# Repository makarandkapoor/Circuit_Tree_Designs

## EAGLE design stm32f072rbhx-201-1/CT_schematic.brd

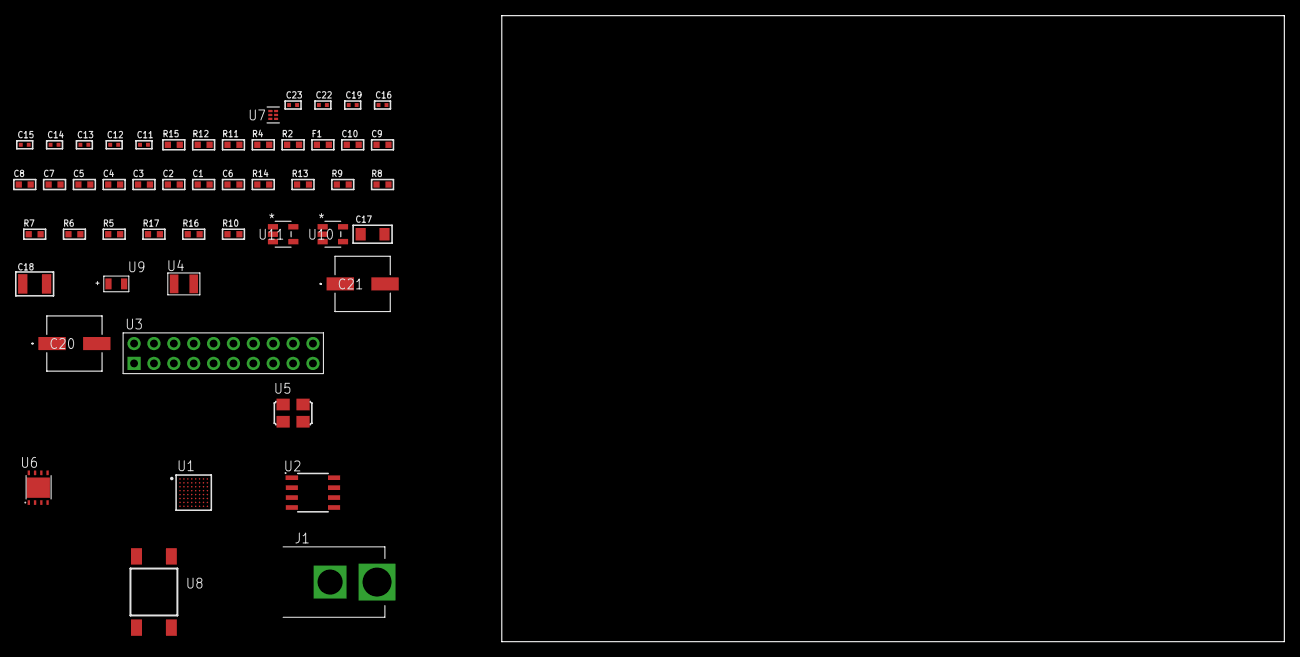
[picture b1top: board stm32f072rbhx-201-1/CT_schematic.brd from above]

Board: 2 copper layers, 100.0 x 80.0 mm, 51 parts (0 on the bottom side), 26 nets, no tracks yet.

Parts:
C1, C10: 1e-06; C0603
C2, C3, C4, C5, C7, C8: 1e-07; C0603
C6: 4.7e-06; C0603
C9: 1e-08; C0603
C11, C12: 1e-11; C0402
C13, C15, C16, C22, C23: 1e-08; C0402
C14, C19: 1e-07; C0402
C17: 1e-05; C1206
C18: 1e-05; C1210
C20, C21: 0.0001; EXV-9H
F1: 240.0; L0603
J1: PJ-037B; PJ-037B_PACKAGE
R2, R12: 1000.0; R0603
R4: 4700.0; R0603
R5, R6, R7, R8, R9, R13, R14: 10000.0; R0603
R10: 100000.0; R0603
R11: 2231.0; R0603
R15: 9100.0; R0603
R16: 680000.0; R0603
R17: 120000.0; R0603
U1: stm32f072rbh6; UFBGA64
U2: AT25020B-SSHL-T; SOIC-8
U3: TST-110-05-T-D-RA
U4: ABS07-32.768KHZ-7-T
U5: ASFL1-25MHZ-NCS; ASFL1
U6: LP3878SDX-ADJ/NOPB; WSON-8
U7: TPS3895ADRYR; SON-6
U8: 4-1437565-2; SW_4-1437565-2
U9: Q65110A2395; LGM67K-G1J2-24-Z
U10, U11: nc7sz125m5x; NC7SZ125M5X

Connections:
CLK_CRYSTAL_U1_A1: C11.1, U1.A1, U4.1
CLK_CRYSTAL_U1_B1: C12.1, U1.B1, U4.2
CLK_U1_C1: U1.C1, U5.3
GND: C1.2, C2.2, C3.2, C4.2, C5.2, C6.2, C7.2, C8.2, C9.2, C10.2, C11.2, C12.2, C13.2, C14.2, C15.2, C16.2, C17.2, C18.2, C19.2, C20.2, C21.2, C22.2, C23.2, J1.2, R2.2, R5.2, R12.2, R15.2, R17.2, U1.C2, U1.D4, U1.D5, U1.D6, U1.F1, U2.4, U3.4, U3.6, U3.8, U3.10, U3.12, U3.14, U3.16, U3.18, U3.20, U5.2, U6.3, U6.PAD, U7.2, U9.C, U10.2, U10.3, U11.1, U11.3
NET_U1_B4: R5.1, U1.B4
NET_U1_E1: R4.1, U1.E1, U11.4
NET_U1_H1: C9.1, C10.1, F1.1, U1.H1
NET_U1_H8: U8.3, U8.4
NET_U2_3: R6.1, U2.3
NET_U2_7: R8.1, U2.7
NET_U6_1: C16.1, U6.1
NET_U6_6: R11.2, R12.1, U6.6
NET_U6_8: R10.1, U6.8
NET_U7_1: R14.1, R15.1, U7.1
NET_U7_3: R16.2, R17.1, U7.3
NET_U7_4: R13.1, U7.4, U10.4, U11.2
NET_U8_1: R2.1, U8.1, U8.2
PROC_SPI1_MISO: U1.A4, U2.2
PROC_SPI1_MOSI: U1.C4, U2.5
PROC_SPI1_NSS: R7.1, U1.A6, U2.1
PROC_SPI1_SCK: U1.A5, U2.6
PROC_SYS_SWCLK: U1.A7, U3.9
PROC_SYS_SWDIO: U1.A8, U3.7
RST_OUT_U3_SRESET_B: R9.1, U3.15, U10.1
VCC_S1_10V3: C17.1, C20.1, C21.1, J1.1, R10.2, U6.4
VCC_TIER1_3V3: C1.1, C2.1, C3.1, C4.1, C5.1, C6.1, C7.1, C8.1, C13.1, C14.1, C15.1, C18.1, C19.1, C22.1, C23.1, F1.2, R4.2, R6.2, R7.2, R8.2, R9.2, R11.1, R13.2, R14.2, R16.1, U1.B2, U1.D2, U1.E4, U1.E5, U1.E6, U2.8, U3.1, U5.4, U6.5, U7.6, U10.5, U11.5

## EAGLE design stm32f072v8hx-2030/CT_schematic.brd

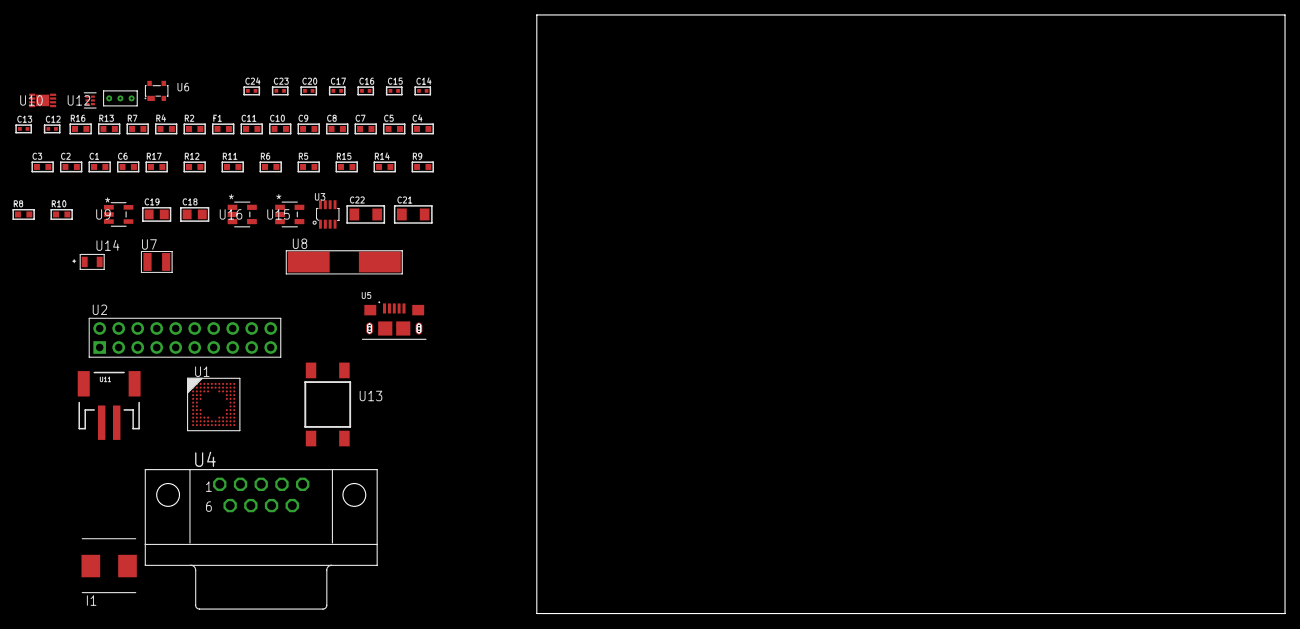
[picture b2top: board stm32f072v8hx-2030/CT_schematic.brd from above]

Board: 2 copper layers, 122.6 x 80.0 mm, 58 parts (0 on the bottom side), 34 nets, no tracks yet.

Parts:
C1, C11: 1e-06; C0603
C2, C3, C4, C5, C7, C8, C9: 1e-07; C0603
C6: 4.7e-06; C0603
C10: 1e-08; C0603
C12, C13, C14, C15: 1e-11; C0402
C16, C17, C20: 1e-07; C0402
C18, C19: 1e-05; C0805
C21, C22: 1e-05; C1206
C23, C24: 1e-08; C0402
F1: 240.0; L0603
I1: 2e-06; WE-HCI_7030/7040/7050
R2: 1000.0; R0603
R4: 4700.0; R0603
R5, R6, R11, R12, R17: 10000.0; R0603
R7: 120.0; R0603
R8: 100000.0; R0603
R9: 220000.0; R0603
R10: 1000000.0; R0603
R13: 9100.0; R0603
R14: 680000.0; R0603
R15: 120000.0; R0603
R16: 2000.0; R0603
U1: stm32f072v8h6; UFBGA100
U2: TST-110-05-T-D-RA
U3: MAX3051EKA+T; SOT-23-8
U4: 182-009-113R531; 182-009-MALE
U5: 10118193-0001LF; FCI_10118193-0001LF
U6: prtr5v0u2ax; SOT143B
U7: ABS07-32.768KHZ-7-T
U8: ABLS-25.000MHZ-B2F-T
U9: ltc3406es5; TSOT-23-5
U10: MCP73831T-2ACI/MC; DFN8_2X3MC
U11: S2B-PH-SM4-TB(LF)(SN); JST-2-SMD
U12: TPS3895ADRYR; SON-6
U13: 4-1437565-2; SW_4-1437565-2
U14: Q65110A2395; LGM67K-G1J2-24-Z
U15, U16: nc7sz125m5x; NC7SZ125M5X
U17: Dummy; DUMMY_PACKAGE_126

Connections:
CLK_CRYSTAL_U1_D1: C12.1, U1.D1, U7.1
CLK_CRYSTAL_U1_E1: C13.1, U1.E1, U7.2
CLK_CRYSTAL_U1_F1: C14.1, U1.F1, U8.1
CLK_CRYSTAL_U1_G1: C15.1, U1.G1, U8.2
GND: C1.2, C2.2, C3.2, C4.2, C5.2, C6.2, C7.2, C8.2, C9.2, C10.2, C11.2, C12.2, C13.2, C14.2, C15.2, C16.2, C17.2, C18.2, C19.1, C19.2, C20.2, C21.2, C22.2, C23.2, C24.2, R2.2, R5.2, R8.2, R9.2, R13.2, R15.2, R16.2, U1.D3, U1.F11, U1.F12, U1.K1, U2.4, U2.6, U2.8, U2.10, U2.12, U2.14, U2.16, U2.18, U2.20, U3.2, U4.5, U5.5, U5.6, U5.7, U5.8, U5.9, U6.1, U9.2, U10.6, U10.9, U11.2, U12.2, U14.C, U15.2, U15.3, U16.1, U16.3, U17.1
INPUT_USBPOWER_5V: C21.1, R17.2, U5.1, U6.4, U10.1, U10.2
NET_U1_A4: R5.1, U1.A4
NET_U1_H2: R4.1, U1.H2, U16.4
NET_U1_M1: C10.1, C11.1, F1.1, U1.M1
NET_U1_M12: U13.3, U13.4
NET_U3_6: R7.2, U3.6
NET_U3_8: R8.1, U3.8
NET_U4_2: R7.2, U3.6, U4.2
NET_U4_3: R7.1, U3.7, U4.3
NET_U9_3: I1.1, U9.3
NET_U9_5: R9.1, R10.1, U9.5
NET_U9_ATNET_3: I1.2, R10.2
NET_U10_5: R17.1, U10.5
NET_U10_8: R16.1, U10.8
NET_U12_1: R12.1, R13.1, U12.1
NET_U12_3: R14.2, R15.1, U12.3
NET_U12_4: R11.1, U12.4, U15.4, U16.2
NET_U13_1: R2.1, U13.1, U13.2
PROC_ADC_IN3: U1.L3, U17.3
PROC_ADC_IN13: U1.K2, U17.2
PROC_CAN_RX: U1.A3, U3.4
PROC_CAN_TX: U1.B3, U3.1
PROC_SYS_SWCLK: U1.A10, U2.9
PROC_SYS_SWDIO: U1.A11, U2.7
PROC_USB_DM: U1.B12, U5.2, U6.3
PROC_USB_DP: U1.A12, U5.3, U6.2
RST_OUT_U2_SRESET_B: R6.1, U2.15, U15.1
VCC_S1_3V7: C18.1, C22.1, U9.4, U10.3, U10.4, U11.1
VCC_TIER1_3V3: C1.1, C2.1, C3.1, C4.1, C5.1, C6.1, C7.1, C8.1, C9.1, C16.1, C17.1, C19.2, C20.1, C23.1, C24.1, F1.2, I1.2, R4.2, R6.2, R10.2, R11.2, R12.2, R14.1, U1.C4, U1.E2, U1.G11, U1.G12, U1.H3, U2.1, U3.3, U12.6, U15.5, U16.5

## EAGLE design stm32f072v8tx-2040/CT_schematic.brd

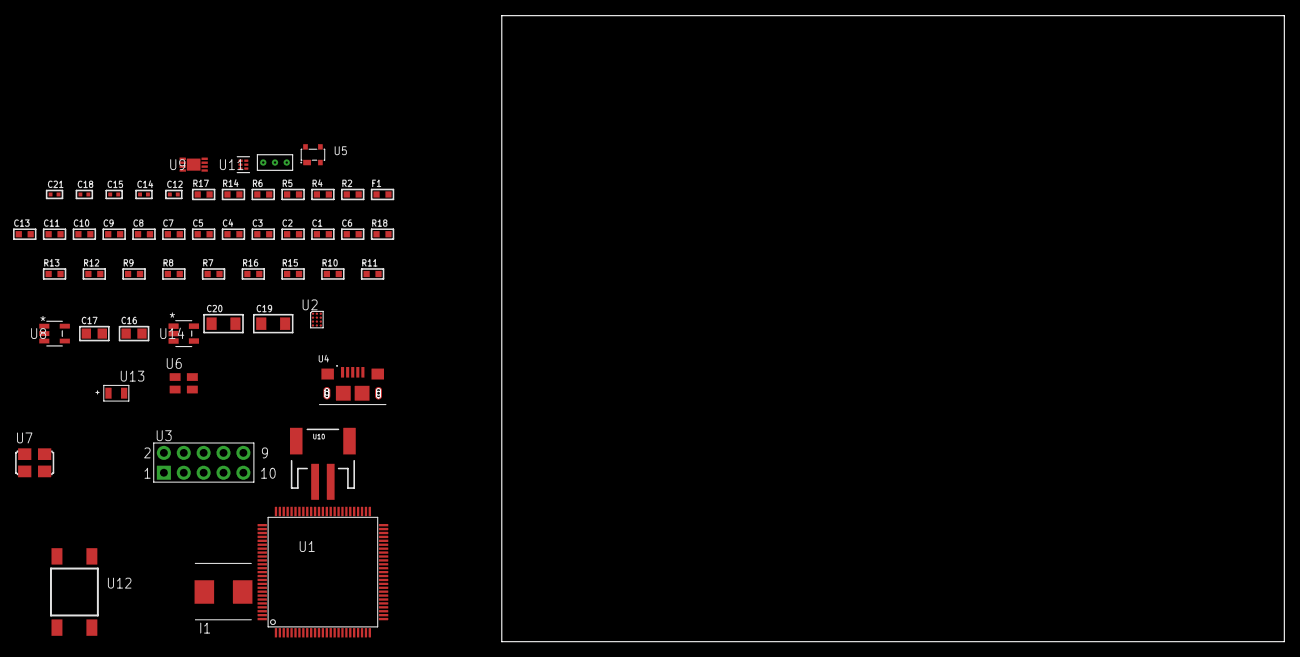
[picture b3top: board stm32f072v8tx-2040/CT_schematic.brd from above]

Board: 2 copper layers, 122.6 x 80.0 mm, 54 parts (0 on the bottom side), 31 nets, no tracks yet.

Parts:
C1, C11, C13: 1e-06; C0603
C2, C3, C4, C5, C7, C8, C9: 1e-07; C0603
C6: 4.7e-06; C0603
C10: 1e-08; C0603
C12, C18: 1e-07; C0402
C14, C15, C21: 1e-08; C0402
C16, C17: 1e-05; C0805
C19, C20: 1e-05; C1206
F1: 240.0; L0603
I1: 2e-06; WE-HCI_7030/7040/7050
R2: 1000.0; R0603
R4: 4700.0; R0603
R5, R6: 2200.0; R0603
R7, R8, R9, R12, R13, R18: 10000.0; R0603
R10: 220000.0; R0603
R11: 1000000.0; R0603
R14: 9100.0; R0603
R15: 680000.0; R0603
R16: 120000.0; R0603
R17: 2000.0; R0603
U1: stm32f072v8t6; LQFP100
U2: TSC2014IYZGT
U3: HTSS-105-01-G-D
U4: 10118193-0001LF; FCI_10118193-0001LF
U5: prtr5v0u2ax; SOT143B
U6: ASEK-32.768KHz-ECST; ASEK
U7: ASFL1-25MHZ-NCS; ASFL1
U8: ltc3406es5; TSOT-23-5
U9: MCP73831T-2ACI/MC; DFN8_2X3MC
U10: S2B-PH-SM4-TB(LF)(SN); JST-2-SMD
U11: TPS3895ADRYR; SON-6
U12: 4-1437565-2; SW_4-1437565-2
U13: Q65110A2395; LGM67K-G1J2-24-Z
U14: nc7sz125m5x; NC7SZ125M5X
U15: Dummy; DUMMY_PACKAGE_119

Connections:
CLK_U1_8: U1.8, U6.3
CLK_U1_12: U1.12, U7.3
GND: C1.2, C2.2, C3.2, C4.2, C5.2, C6.2, C7.2, C8.2, C9.2, C10.2, C11.2, C12.2, C13.2, C14.2, C15.2, C16.2, C17.1, C17.2, C18.2, C19.2, C20.2, C21.2, R2.2, R7.2, R10.2, R14.2, R16.2, R17.2, U1.20, U1.27, U1.49, U1.74, U1.99, U2.B2, U2.D2, U3.9, U4.5, U4.6, U4.7, U4.8, U4.9, U5.1, U6.2, U7.2, U8.2, U9.6, U9.9, U10.2, U11.2, U13.C, U14.1, U14.3, U15.1
INPUT_USBPOWER_5V: C19.1, R18.2, U4.1, U5.4, U9.1, U9.2
NET_U1_14: R4.1, U1.14, U14.4
NET_U1_21: C10.1, C11.1, F1.1, U1.21
NET_U1_92: R5.1, U1.92, U2.D1
NET_U1_93: R6.1, U1.93, U2.C1
NET_U1_94: R7.1, U1.94
NET_U1_98: U12.3, U12.4
NET_U2_B1: R9.1, U2.B1
NET_U2_C2: R8.1, U2.C2
NET_U3_3: U2.B3, U3.3
NET_U3_4: U2.D3, U3.4
NET_U3_5: U2.A3, U3.5
NET_U3_6: U2.C3, U3.6
NET_U8_3: I1.1, U8.3
NET_U8_5: R10.1, R11.1, U8.5
NET_U8_ATNET_3: I1.2, R11.2
NET_U9_5: R18.1, U9.5
NET_U9_8: R17.1, U9.8
NET_U11_1: R13.1, R14.1, U11.1
NET_U11_3: R15.2, R16.1, U11.3
NET_U11_4: R12.1, U11.4, U14.2
NET_U12_1: R2.1, U12.1, U12.2
PROC_TIM1_CH2: U1.42, U15.2
PROC_TIM1_CH4: U1.45, U15.3
PROC_USB_DM: U1.70, U4.2, U5.3
PROC_USB_DP: U1.71, U4.3, U5.2
VCC_S1_3V7: C16.1, C20.1, U8.4, U9.3, U9.4, U10.1
VCC_TIER1_3V3: C1.1, C2.1, C3.1, C4.1, C5.1, C6.1, C7.1, C8.1, C9.1, C12.1, C13.1, C14.1, C15.1, C17.2, C18.1, C21.1, F1.2, I1.2, R4.2, R5.2, R6.2, R8.2, R9.2, R11.2, R12.2, R13.2, R15.1, U1.6, U1.28, U1.50, U1.75, U1.100, U2.A2, U6.4, U7.4, U11.6, U14.5

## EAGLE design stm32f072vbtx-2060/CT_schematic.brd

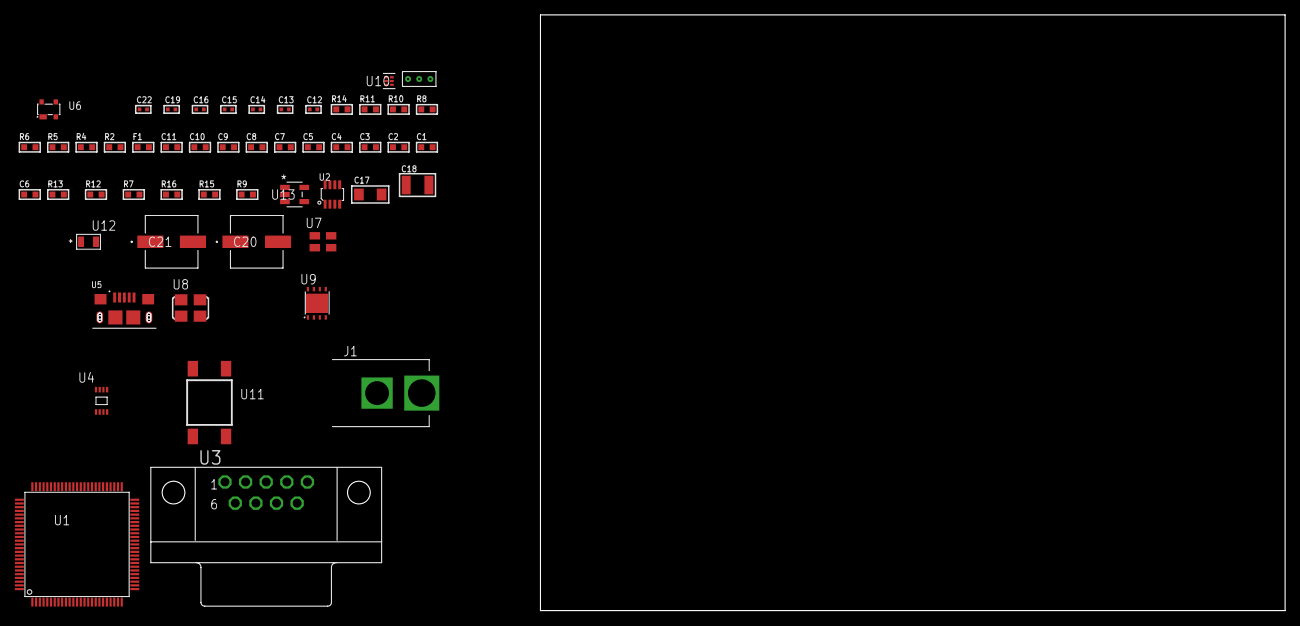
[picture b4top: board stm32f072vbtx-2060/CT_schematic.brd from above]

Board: 2 copper layers, 159.4 x 80.0 mm, 52 parts (0 on the bottom side), 29 nets, no tracks yet.

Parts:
C1, C11: 1e-06; C0603
C2, C3, C4, C5, C7, C8, C9: 1e-07; C0603
C6: 4.7e-06; C0603
C10: 1e-08; C0603
C12, C19: 1e-07; C0402
C13, C14, C15, C16, C22: 1e-08; C0402
C17: 1e-05; C1206
C18: 1e-05; C1210
C20, C21: 0.0001; EXV-9H
F1: 240.0; L0603
J1: PJ-037B; PJ-037B_PACKAGE
R2, R11: 1000.0; R0603
R4: 4700.0; R0603
R5, R6: 2200.0; R0603
R7, R12, R13: 10000.0; R0603
R8: 120.0; R0603
R9: 100000.0; R0603
R10: 2231.0; R0603
R14: 9100.0; R0603
R15: 680000.0; R0603
R16: 120000.0; R0603
U1: stm32f072vbt7; LQFP100
U2: MAX3051EKA+T; SOT-23-8
U3: 182-009-113R531; 182-009-MALE
U4: 24AA00T-I/MNY; TDFN-8/6MM
U5: 10118193-0001LF; FCI_10118193-0001LF
U6: prtr5v0u2ax; SOT143B
U7: ASEK-32.768KHz-ECST; ASEK
U8: ASFL1-25MHZ-NCS; ASFL1
U9: LP3878SDX-ADJ/NOPB; WSON-8
U10: TPS3895ADRYR; SON-6
U11: 4-1437565-2; SW_4-1437565-2
U12: Q65110A2395; LGM67K-G1J2-24-Z
U13: nc7sz125m5x; NC7SZ125M5X
U14: Dummy; DUMMY_PACKAGE_115

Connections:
CLK_U1_8: U1.8, U7.3
CLK_U1_12: U1.12, U8.3
GND: C1.2, C2.2, C3.2, C4.2, C5.2, C6.2, C7.2, C8.2, C9.2, C10.2, C11.2, C12.2, C13.2, C14.2, C15.2, C16.2, C17.2, C18.2, C19.2, C20.2, C21.2, C22.2, J1.2, R2.2, R7.2, R11.2, R14.2, R16.2, U1.20, U1.27, U1.49, U1.74, U1.99, U2.2, U2.8, U3.5, U4.4, U5.5, U5.6, U5.7, U5.8, U5.9, U6.1, U7.2, U8.2, U9.3, U9.PAD, U10.2, U12.C, U13.1, U13.3, U14.1
NET_U1_14: R4.1, U1.14, U13.4
NET_U1_21: C10.1, C11.1, F1.1, U1.21
NET_U1_75: C9.1, U1.75
NET_U1_92: R5.1, U1.92, U4.6
NET_U1_93: R6.1, U1.93, U4.5
NET_U1_94: R7.1, U1.94
NET_U1_98: U11.3, U11.4
NET_U2_6: R8.2, U2.6
NET_U3_2: R8.2, U2.6, U3.2
NET_U3_3: R8.1, U2.7, U3.3
NET_U6_4: U5.1, U6.4
NET_U9_1: C16.1, U9.1
NET_U9_6: R10.2, R11.1, U9.6
NET_U9_8: R9.1, U9.8
NET_U10_1: R13.1, R14.1, U10.1
NET_U10_3: R15.2, R16.1, U10.3
NET_U10_4: R12.1, U10.4, U13.2
NET_U11_1: R2.1, U11.1, U11.2
PROC_CAN_RX: U1.81, U2.4
PROC_CAN_TX: U1.82, U2.1
PROC_TIM1_CH2: U1.42, U14.2
PROC_TIM1_CH4: U1.45, U14.3
PROC_USB_DM: U1.70, U5.2, U6.3
PROC_USB_DP: U1.71, U5.3, U6.2
VCC_S1_7V6: C17.1, C20.1, C21.1, J1.1, R9.2, U9.4
VCC_TIER1_3V3: C1.1, C2.1, C3.1, C4.1, C5.1, C6.1, C7.1, C8.1, C12.1, C13.1, C14.1, C15.1, C18.1, C19.1, C22.1, F1.2, R4.2, R5.2, R6.2, R10.1, R12.2, R13.2, R15.1, U1.6, U1.28, U1.50, U1.100, U2.3, U4.8, U7.4, U8.4, U9.5, U10.6, U13.5

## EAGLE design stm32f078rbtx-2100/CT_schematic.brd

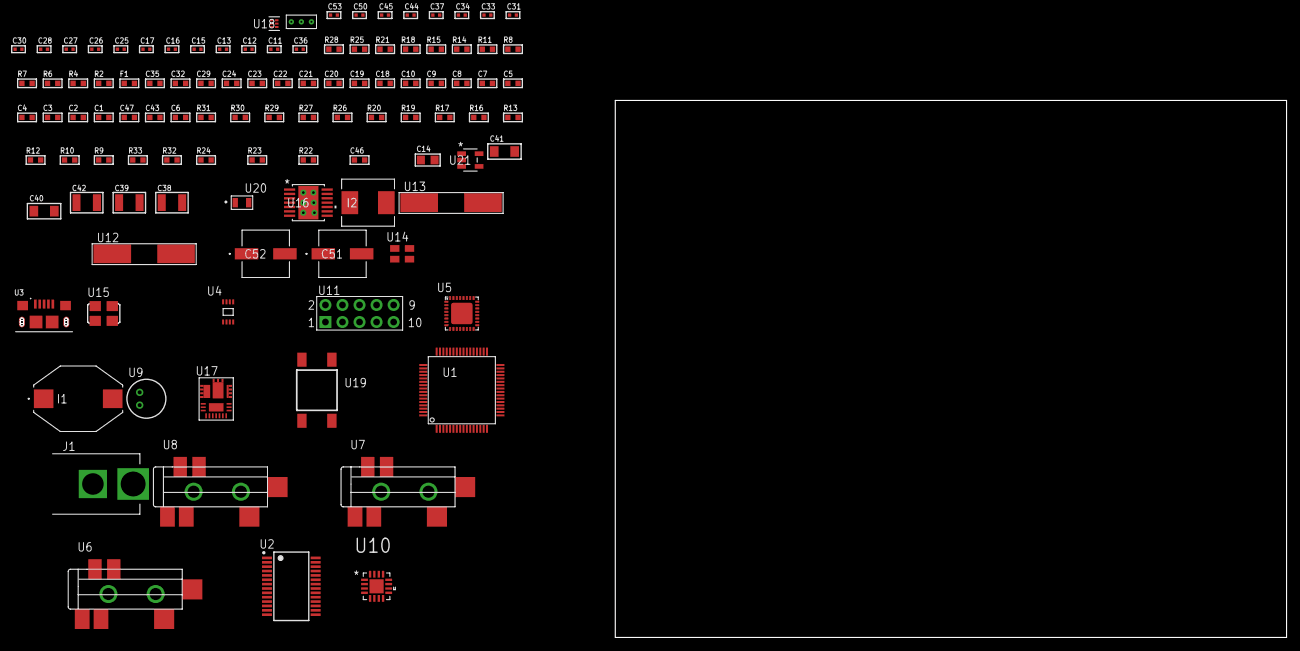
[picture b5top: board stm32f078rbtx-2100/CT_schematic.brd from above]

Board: 2 copper layers, 107 parts (0 on the bottom side), 73 nets, no tracks yet.

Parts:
C1, C10, C18, C19, C20, C21, C22, C23, C24, C29, C32, C35: 1e-06; C0603
C2, C3, C4, C5, C7, C8: 1e-07; C0603
C6: 4.7e-06; C0603
C9: 1e-08; C0603
C11, C12: 1e-11; C0402
C13, C15, C16, C25, C26, C27, C28, C30, C31, C37, C44, C45, C50: 1e-07; C0402
C14: 4.7e-06; C0805
C17, C33, C34, C53: 1e-08; C0402
C36: 3.3e-09; C0402
C38, C39: 2.2e-05; C1210
C40, C41: 1e-05; C1206
C42: 0.0001; C1210
C43: 2.2e-06; C0603
C46: 7.8444498006919e-09; R0603
C47: 2.7e-07; C0603
C51, C52: 0.0001; EXV-9H
F1: 240.0; L0603
I1: 1e-05; IND_PM3316
I2: 6.8e-07; IND25X25CZ
J1: PJ-037B; PJ-037B_PACKAGE
R2: 1000.0; R0603
R4, R11: 4700.0; R0603
R6, R7, R8: 2200.0; R0603
R9, R10, R12, R13, R16, R17, R29, R30: 10000.0; R0603
R14, R15: 1270.0; R0603
R18: 47.0; R0603
R19: 30000.0; R0603
R20: 22000.0; R0603
R21: 0.1; R0603
R22: 4030.2416170974; R0603
R23: 719.68600305311; R0603
R24: 64.984347826087; R0603
R25: 130.0; R0603
R26: 39000.0; R0603
R27: 49900.0; R0603
R28: 5600.0; R0603
R31: 82000.0; R0603
R32: 300000.0; R0603
R33: 120000.0; R0603
U1: stm32f078rbt7; LQFP64
U2: FT232RL-REEL; SSOP-28
U3: 10118193-0001LF; FCI_10118193-0001LF
U4: 24AA08T-I/MNY; TDFN-8/6MM
U5: SGTL5000XNAA3; QFN-32
U6, U7, U8: SJ-43515TS-SMT-TR
U9: WM-64PCT; WM-64PC
U10: TSC2013QRSARQ1; QFN65P400X400X100-17N
U11: HTSS-105-01-G-D
U12: ABLS-25.000MHZ-B2F-T
U13: ABLS-12.000MHZ-B4-T
U14: ASEK-2-32.768KHz-ECST; ASEK
U15: ASFL-24.57MHZ-NCS; ASFL1
U16: tps54225PWP; HTSSOP14
U17: IR3899MTR1PBF
U18: TPS3895ADRYR; SON-6
U19: 4-1437565-2; SW_4-1437565-2
U20: Q65110A2395; LGM67K-G1J2-24-Z
U21: nc7sz125m5x; NC7SZ125M5X
U22: Dummy; DUMMY_PACKAGE_213

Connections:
CLK_CRYSTAL_U1_5: C11.1, U1.5, U12.1
CLK_CRYSTAL_U1_6: C12.1, U1.6, U12.2
CLK_CRYSTAL_U2_27: U2.27, U13.1
CLK_CRYSTAL_U2_28: U2.28, U13.2
CLK_U1_3: U1.3, U14.3
CLK_U5_21: U5.21, U15.3
GND: C1.2, C2.2, C3.2, C4.2, C5.2, C6.2, C7.2, C8.2, C9.2, C10.2, C11.2, C12.2, C13.2, C14.2, C15.2, C16.2, C17.2, C25.2, C26.2, C27.2, C28.2, C29.2, C33.2, C34.2, C35.2, C36.2, C38.2, C39.2, C40.2, C41.2, C43.2, C44.2, C45.2, C50.2, C51.2, C52.2, C53.2, J1.2, R2.2, R9.2, R10.2, R13.2, R15.2, R20.2, R21.1, R21.2, R23.2, R26.2, R28.2, R31.2, R33.2, U1.12, U1.18, U1.31, U1.47, U1.63, U2.7, U2.18, U2.21, U2.25, U2.26, U3.5, U3.6, U3.7, U3.8, U3.9, U4.4, U4.7, U5.1, U5.3, U5.7, U5.EXP, U7.1, U8.1, U9.2, U10.17, U11.9, U14.2, U15.2, U16.5, U16.8, U16.9, U16.15, U17.4, U17.11, U17.17, U18.2, U20.C, U21.1, U21.3, U22.1
NET_U1_7: R4.1, U1.7, U21.4
NET_U1_13: C9.1, C10.1, F1.1, U1.13
NET_U1_28: R10.1, U1.28
NET_U1_29: R7.1, U1.29, U4.6
NET_U1_30: R8.1, U1.30, U4.5
NET_U1_59: R6.1, U1.59, U10.1
NET_U1_60: R9.1, U1.60
NET_U1_62: U19.3, U19.4
NET_U2_14: R12.1, U2.14
NET_U2_17: C15.1, U2.17
NET_U2_19: R13.1, U2.19
NET_U3_1: R11.1, U3.1
NET_U3_2: U2.16, U3.2
NET_U3_3: U2.15, U3.3
NET_U5_10: C28.1, U5.10
NET_U5_29: R14.1, U5.29
NET_U5_31: R15.1, U5.31
NET_U6_1: U5.4, U6.1
NET_U6_2: U5.2, U6.2
NET_U6_5: U5.6, U6.5
NET_U7_2: C19.1, U7.2
NET_U7_5: C18.1, U7.5
NET_U8_2: C21.1, C22.1, U8.2
NET_U8_5: C20.1, U8.5
NET_U8_13: C21.2, C22.2
NET_U9_1: C23.1, C24.1, C29.1, U5.16, U9.1
NET_U9_15: C23.2, C24.2
NET_U10_4: R17.1, U10.4
NET_U10_5: R16.1, U10.5
NET_U10_9: C30.2, C31.2, C32.2, R18.2, U10.9
NET_U10_15: R18.1, U10.8, U10.15
NET_U11_3: U10.12, U11.3
NET_U11_4: U10.14, U11.4
NET_U11_5: U10.11, U11.5
NET_U11_6: U10.13, U11.6
NET_U16_2: R19.2, R20.1, U16.2
NET_U16_3: C35.1, U16.3
NET_U16_4: C36.1, U16.4
NET_U16_10: C37.1, I1.1, U16.10, U16.11
NET_U16_12: C37.2, U16.12
NET_U17_1: C46.1, R22.1, R23.1, R24.1, R25.1, U17.1, U17.8
NET_U17_2: C45.1, U17.2
NET_U17_3: C46.2, C47.1, C47.2, U17.3
NET_U17_5: R26.1, U17.5
NET_U17_10: C43.1, U17.10
NET_U17_12: C42.1, I2.1, U17.12
NET_U17_14: C42.2, U17.14
NET_U17_15: R27.1, R28.1, U17.15
NET_U17_ATNET_3: I2.2, R22.2
NET_U17_ATNET_4: C47.2, R24.2
NET_U18_1: R30.1, R31.1, U18.1
NET_U18_3: R32.2, R33.1, U18.3
NET_U18_4: R29.1, U18.4, U21.2
NET_U19_1: R2.1, U19.1, U19.2
PROC_I2S1_CK: U1.21, U5.24
PROC_I2S1_SD: U1.23, U5.26
PROC_I2S1_WS: U1.20, U5.23
PROC_TIM1_CH1: U1.41, U22.3
PROC_TIM1_CH2N: U1.26, U22.2
PROC_USART1_CTS: U1.44, U2.3
PROC_USART1_RTS: U1.45, U2.11
PROC_USART1_RX: U1.43, U2.1
PROC_USART1_TX: U1.42, U2.5
VCC_S1_16V1: C40.1, C41.1, C44.1, C51.1, C52.1, J1.1, R27.2, U16.7, U16.13, U16.14, U17.9
VCC_TIER1_1V8: C1.1, C2.1, C3.1, C4.1, C5.1, C6.1, C7.1, C8.1, C16.1, C17.1, C25.1, C26.1, C27.1, C30.1, C33.1, C38.1, C39.1, C50.1, C53.1, F1.2, I1.2, R4.2, R6.2, R7.2, R8.2, R14.2, R16.2, R17.2, R19.1, R29.2, R30.2, R32.1, U1.1, U1.19, U1.32, U1.48, U1.64, U2.4, U4.8, U5.5, U5.20, U5.30, U10.7, U14.4, U16.1, U18.6, U21.5
VCC_TIER1_3V3: C13.1, C14.1, C31.1, C32.1, C34.1, I2.2, R12.2, R22.2, U2.20, U10.10, U15.4

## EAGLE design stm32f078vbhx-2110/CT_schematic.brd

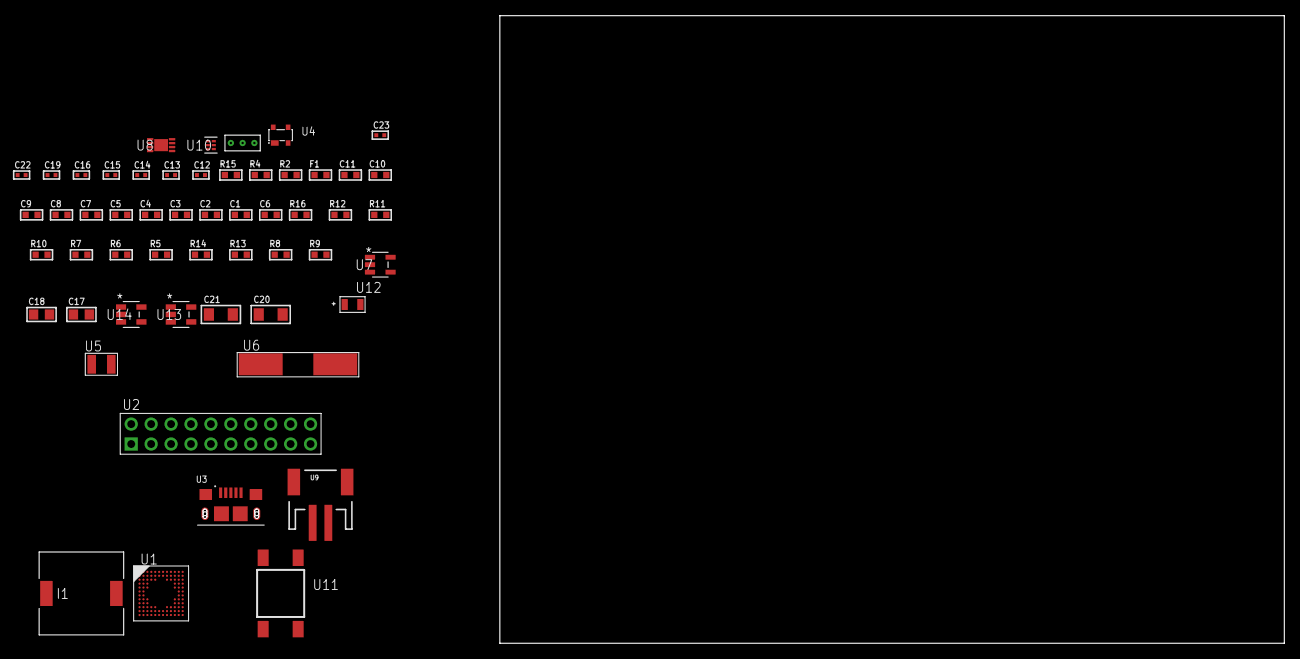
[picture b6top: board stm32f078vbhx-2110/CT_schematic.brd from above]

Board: 2 copper layers, 54 parts (0 on the bottom side), 29 nets, no tracks yet.

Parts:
C1, C11: 1e-06; C0603
C2, C3, C4, C5, C7, C8, C9: 1e-07; C0603
C6: 4.7e-06; C0603
C10: 1e-08; C0603
C12, C13, C14, C15: 1e-11; C0402
C16, C19: 1e-07; C0402
C17, C18: 1e-05; C0805
C20, C21: 1e-05; C1206
C22, C23: 1e-08; C0402
F1: 240.0; L0603
I1: 5.2e-06; DR1040
R2: 1000.0; R0603
R4: 4700.0; R0603
R5, R6, R7, R10, R11, R16: 10000.0; R0603
R8: 490000.0; R0603
R9: 1000000.0; R0603
R12: 82000.0; R0603
R13: 300000.0; R0603
R14: 120000.0; R0603
R15: 2000.0; R0603
U1: stm32f078vbh7; UFBGA100
U2: TST-110-05-T-D-RA
U3: 10118193-0001LF; FCI_10118193-0001LF
U4: prtr5v0u2ax; SOT143B
U5: ABS07-32.768KHZ-7-T
U6: ABLS-25.000MHZ-B2F-T
U7: ltc3406es5; TSOT-23-5
U8: MCP73831T-2ACI/MC; DFN8_2X3MC
U9: S2B-PH-SM4-TB(LF)(SN); JST-2-SMD
U10: TPS3895ADRYR; SON-6
U11: 4-1437565-2; SW_4-1437565-2
U12: Q65110A2395; LGM67K-G1J2-24-Z
U13, U14: nc7sz125m5x; NC7SZ125M5X
U15: Dummy; DUMMY_PACKAGE_116

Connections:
CLK_CRYSTAL_U1_D1: C12.1, U1.D1, U5.1
CLK_CRYSTAL_U1_E1: C13.1, U1.E1, U5.2
CLK_CRYSTAL_U1_F1: C14.1, U1.F1, U6.1
CLK_CRYSTAL_U1_G1: C15.1, U1.G1, U6.2
GND: C1.2, C2.2, C3.2, C4.2, C5.2, C6.2, C7.2, C8.2, C9.2, C10.2, C11.2, C12.2, C13.2, C14.2, C15.2, C16.2, C17.2, C18.1, C18.2, C19.2, C20.2, C21.2, C22.2, C23.2, R2.2, R5.2, R6.2, R8.2, R12.2, R14.2, R15.2, U1.D3, U1.F11, U1.F12, U1.K1, U2.4, U2.6, U2.8, U2.10, U2.12, U2.14, U2.16, U2.18, U2.20, U3.5, U3.6, U3.7, U3.8, U3.9, U4.1, U7.2, U8.6, U8.9, U9.2, U10.2, U12.C, U13.2, U13.3, U14.1, U14.3, U15.1
INPUT_USBPOWER_5V: C20.1, R16.2, U3.1, U4.4, U8.1, U8.2
NET_U1_A4: R5.1, U1.A4
NET_U1_H2: R4.1, U1.H2, U14.4
NET_U1_L6: R6.1, U1.L6
NET_U1_M1: C10.1, C11.1, F1.1, U1.M1
NET_U1_M12: U11.3, U11.4
NET_U7_3: I1.1, U7.3
NET_U7_5: R8.1, R9.1, U7.5
NET_U7_ATNET_3: I1.2, R9.2
NET_U8_5: R16.1, U8.5
NET_U8_8: R15.1, U8.8
NET_U10_1: R11.1, R12.1, U10.1
NET_U10_3: R13.2, R14.1, U10.3
NET_U10_4: R10.1, U10.4, U13.4, U14.2
NET_U11_1: R2.1, U11.1, U11.2
PROC_SYS_SWCLK: U1.A10, U2.9
PROC_SYS_SWDIO: U1.A11, U2.7
PROC_TIM1_CH2: U1.D10, U15.2
PROC_TIM1_CH2N: U1.K11, U15.3
PROC_USB_DM: U1.B12, U3.2, U4.3
PROC_USB_DP: U1.A12, U3.3, U4.2
RST_OUT_U2_SRESET_B: R7.1, U2.15, U13.1
VCC_S1_3V7: C17.1, C21.1, U7.4, U8.3, U8.4, U9.1
VCC_TIER1_1V8: C1.1, C2.1, C3.1, C4.1, C5.1, C6.1, C7.1, C8.1, C9.1, C16.1, C18.2, C19.1, C22.1, C23.1, F1.2, I1.2, R4.2, R7.2, R9.2, R10.2, R11.2, R13.1, U1.C4, U1.E2, U1.G11, U1.G12, U1.H3, U2.1, U10.6, U13.5, U14.5

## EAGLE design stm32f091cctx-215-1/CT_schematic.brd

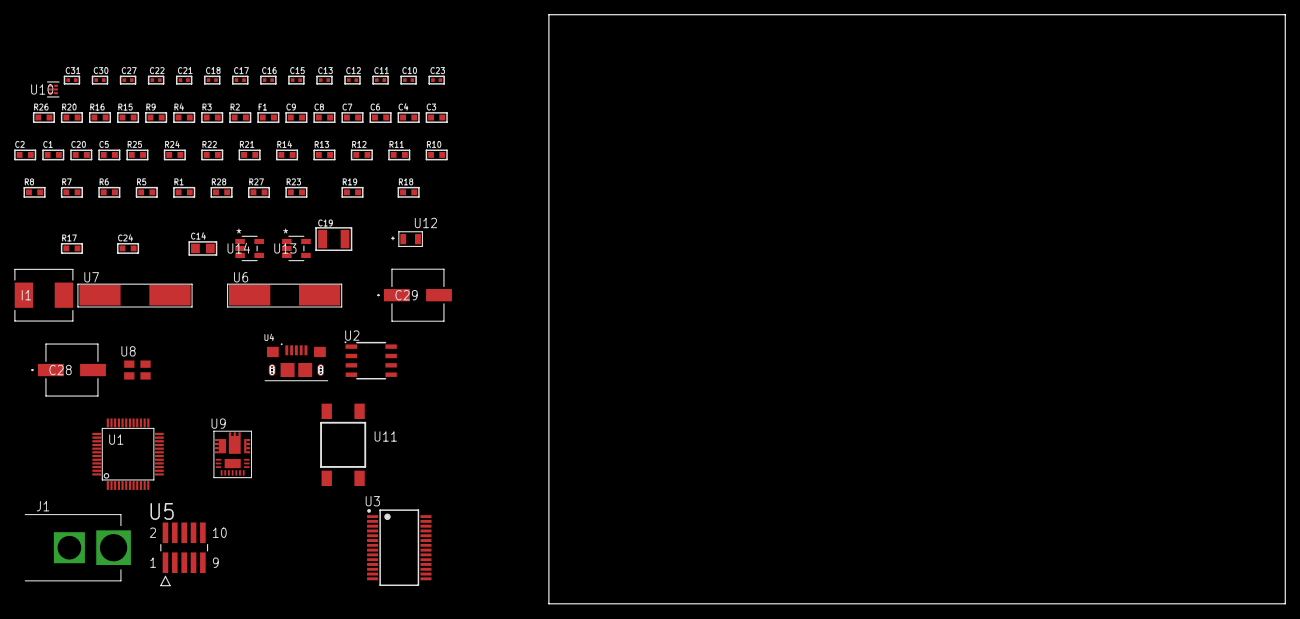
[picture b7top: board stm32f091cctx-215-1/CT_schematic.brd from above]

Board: 2 copper layers, 74 parts (0 on the bottom side), 47 nets, no tracks yet.

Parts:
C1, C9: 1e-06; C0603
C2, C3, C4, C6, C7: 1e-07; C0603
C5: 4.7e-06; C0603
C8: 1e-08; C0603
C10, C11: 1e-11; C0402
C12, C18, C30, C31: 1e-08; C0402
C13, C15, C16, C17, C21, C22, C27: 1e-07; C0402
C14: 4.7e-06; C0805
C19: 0.0001; C1210
C20: 2.2e-06; C0603
C23: 8.2e-09; C0402
C24: 2.724074888439e-07; R0603
C28, C29: 0.0001; EXV-9H
F1: 240.0; L0603
I1: 6.8e-07; IND25X25CZ
J1: PJ-037B; PJ-037B_PACKAGE
R1, R5, R6, R7, R8, R10, R11, R12, R13, R14, R24, R25: 10000.0; R0603
R2: 1000.0; R0603
R3: 1600.5; R0603
R4, R9: 4700.0; R0603
R15: 5.0; R0603
R16: 0.1; R0603
R17: 4030.2416170974; R0603
R18: 719.68600305311; R0603
R19: 63.795609756098; R0603
R20: 130.0; R0603
R21: 39000.0; R0603
R22: 49900.0; R0603
R23: 5286.7027027027; R0603
R26: 9100.0; R0603
R27: 680000.0; R0603
R28: 120000.0; R0603
U1: stm32f091cct6; LQFP48
U2: AT25010B-SSHL-T; SOIC-8
U3: FT232RL-REEL; SSOP-28
U4: 10118193-0001LF; FCI_10118193-0001LF
U5: FTSH-105-01-L-DV-K; SAMTEC_FTSH-105-01-L-DV-K
U6: ABLS-25.000MHZ-B2F-T
U7: ABLS-12.000MHZ-B4-T
U8: ASEK-32.768KHz-ECST; ASEK
U9: IR3899MTR1PBF
U10: TPS3895ADRYR; SON-6
U11: 4-1437565-2; SW_4-1437565-2
U12: Q65110A2395; LGM67K-G1J2-24-Z
U13, U14: nc7sz125m5x; NC7SZ125M5X

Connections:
CLK_CRYSTAL_U1_5: C10.1, U1.5, U6.1
CLK_CRYSTAL_U1_6: C11.1, U1.6, U6.2
CLK_CRYSTAL_U3_27: U3.27, U7.1
CLK_CRYSTAL_U3_28: U3.28, U7.2
CLK_U1_3: U1.3, U8.3
GND: C1.2, C2.2, C3.2, C4.2, C5.2, C6.2, C7.2, C8.2, C9.2, C10.2, C11.2, C12.2, C13.2, C14.2, C15.2, C16.2, C17.2, C18.2, C20.2, C21.2, C22.2, C27.2, C28.2, C29.2, C30.2, C31.2, J1.2, R2.2, R5.2, R11.2, R15.2, R16.1, R16.2, R18.2, R21.2, R23.2, R26.2, R28.2, U1.8, U1.23, U1.35, U1.47, U2.4, U3.7, U3.18, U3.21, U3.25, U3.26, U4.5, U4.6, U4.7, U4.8, U4.9, U5.3, U5.5, U8.2, U9.4, U9.11, U9.17, U10.2, U12.C, U13.2, U13.3, U14.1, U14.3
NET_U1_7: R4.1, U1.7, U14.4
NET_U1_9: C8.1, C9.1, F1.1, U1.9
NET_U1_44: R5.1, U1.44
NET_U1_45: R3.1, U1.45, U12.A
NET_U1_46: R1.1, U1.46, U11.3, U11.4
NET_U2_3: R6.1, U2.3
NET_U2_7: R8.1, U2.7
NET_U3_14: R10.1, U3.14
NET_U3_17: C15.1, U3.17
NET_U3_19: R11.1, U3.19
NET_U4_1: R9.1, U4.1
NET_U4_2: U3.16, U4.2
NET_U4_3: U3.15, U4.3
NET_U5_9: R15.1, U5.9
NET_U9_1: C23.1, R17.1, R18.1, R19.1, R20.1, U9.1, U9.8
NET_U9_2: C22.1, U9.2
NET_U9_3: C23.2, C24.1, C24.2, U9.3
NET_U9_5: R21.1, U9.5
NET_U9_10: C20.1, U9.10
NET_U9_12: C19.1, I1.1, U9.12
NET_U9_14: C19.2, U9.14
NET_U9_15: R22.1, R23.1, U9.15
NET_U9_ATNET_3: I1.2, R17.2
NET_U9_ATNET_4: C24.2, R19.2
NET_U10_1: R25.1, R26.1, U10.1
NET_U10_3: R27.2, R28.1, U10.3
NET_U10_4: R24.1, U10.4, U13.4, U14.2
NET_U11_1: R2.1, U11.1, U11.2
PROC_SPI1_MISO: U1.16, U2.2
PROC_SPI1_MOSI: U1.17, U2.5
PROC_SPI1_NSS: R7.1, U1.14, U2.1
PROC_SPI1_SCK: U1.15, U2.6
PROC_SYS_SWCLK: R13.1, U1.37, U5.4
PROC_SYS_SWDIO: R14.1, U1.34, U5.2
PROC_USART1_CTS: U1.32, U3.3
PROC_USART1_RTS: U1.33, U3.11
PROC_USART1_RX: U1.31, U3.1
PROC_USART1_TX: U1.30, U3.5
RST_OUT_U5_JTAG_RST_B: R12.1, U5.10, U13.1
VCC_S1_16V4: C21.1, C28.1, C29.1, J1.1, R22.2, U9.9
VCC_TIER1_3V3: C1.1, C2.1, C3.1, C4.1, C5.1, C6.1, C7.1, C12.1, C13.1, C14.1, C16.1, C17.1, C18.1, C27.1, C30.1, C31.1, F1.2, I1.2, R1.2, R3.2, R4.2, R6.2, R7.2, R8.2, R10.2, R12.2, R13.2, R14.2, R17.2, R24.2, R25.2, R27.1, U1.1, U1.24, U1.36, U1.48, U2.8, U3.4, U3.20, U5.1, U8.4, U10.6, U13.5, U14.5

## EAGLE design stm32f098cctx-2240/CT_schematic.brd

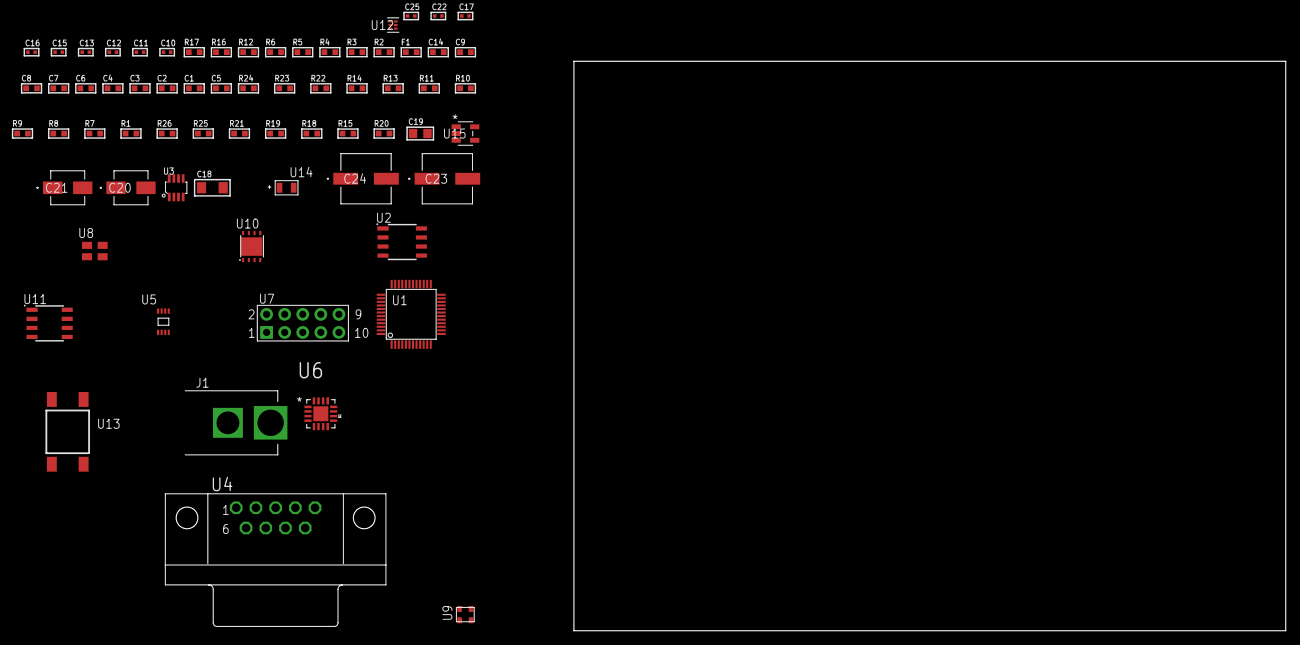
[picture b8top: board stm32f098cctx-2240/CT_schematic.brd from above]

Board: 2 copper layers, 100.0 x 80.0 mm, 68 parts (0 on the bottom side), 44 nets, no tracks yet.

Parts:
C1, C9, C14: 1e-06; C0603
C2, C3, C4, C6, C7: 1e-07; C0603
C5: 4.7e-06; C0603
C8: 1e-08; C0603
C10, C12, C15, C16, C17, C25: 1e-08; C0402
C11, C13, C22: 1e-07; C0402
C18: 1e-05; C1206
C19: 1e-05; C0805
C20: 1e-06; EXV-9B
C21: 2.2e-06; EXV-9B
C23, C24: 0.0001; EXV-9H
F1: 240.0; L0603
J1: PJ-037B; PJ-037B_PACKAGE
R1, R7, R8, R9, R10, R11, R13, R14, R22, R23: 10000.0; R0603
R2, R17: 1000.0; R0603
R3: 910.0; R0603
R4: 4700.0; R0603
R5, R6: 2200.0; R0603
R12: 120.0; R0603
R15, R18, R19, R21: 100000.0; R0603
R16: 806.0; R0603
R20: 164658.62; R0603
R24: 82000.0; R0603
R25: 300000.0; R0603
R26: 120000.0; R0603
U1: stm32f098cct7; LQFP48
U2: AT25M01-SSHM-T; SOIC-8
U3: MAX3051EKA+T; SOT-23-8
U4: 182-009-113R531; 182-009-MALE
U5: 24AA00T-I/MNY; TDFN-8/6MM
U6: TSC2008TRGVRQ1; QFN65P400X400X100-17N
U7: HTSS-105-01-G-D
U8: ASEK-2-32.768KHz-ECST; ASEK
U9: ASDMB-25.000MHZ-EC-T; ASDMB-XX.XXXXMHZ-XX-XX-XXX
U10: LP3878SDX-ADJ/NOPB; WSON-8
U11: LP2954AIMX/NOPB; LP2954
U12: TPS3895ADRYR; SON-6
U13: 4-1437565-2; SW_4-1437565-2
U14: Q65110A2395; LGM67K-G1J2-24-Z
U15: nc7sz125m5x; NC7SZ125M5X

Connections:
CLK_U1_3: U1.3, U8.3
CLK_U1_5: U1.5, U9.3
GND: C1.2, C2.2, C3.2, C4.2, C5.2, C6.2, C7.2, C8.2, C9.2, C10.2, C11.2, C12.2, C13.2, C14.2, C15.2, C16.2, C17.2, C18.2, C19.2, C20.2, C21.2, C22.2, C23.2, C24.2, C25.2, J1.2, R2.2, R7.2, R8.2, R17.2, R21.2, R24.2, R26.2, U1.8, U1.23, U1.35, U1.47, U2.4, U3.2, U3.8, U4.5, U5.4, U6.10, U6.12, U6.17, U7.9, U8.2, U9.2, U10.3, U10.PAD, U11.4, U12.2, U14.C, U15.1, U15.3
NET_U1_6: R5.1, U1.6, U5.6
NET_U1_7: R4.1, U1.7, U15.4
NET_U1_9: C8.1, C9.1, F1.1, U1.9
NET_U1_20: R8.1, U1.20
NET_U1_31: R6.1, U1.31, U5.5
NET_U1_44: R7.1, U1.44
NET_U1_45: R3.1, U1.45, U14.A
NET_U1_46: R1.1, U1.46, U13.3, U13.4
NET_U2_3: R9.1, U2.3
NET_U2_7: R11.1, U2.7
NET_U3_6: R12.2, U3.6
NET_U4_2: R12.2, U3.6, U4.2
NET_U4_3: R12.1, U3.7, U4.3
NET_U6_15: R14.1, U6.15
NET_U7_3: U6.7, U7.3
NET_U7_4: U6.9, U7.4
NET_U7_5: U6.6, U7.5
NET_U7_6: U6.8, U7.6
NET_U10_1: C17.1, U10.1
NET_U10_6: R16.2, R17.1, U10.6
NET_U10_8: R15.1, U10.8
NET_U11_3: R19.1, U11.3
NET_U11_5: R18.1, U11.5
NET_U11_7: R20.2, R21.1, U11.7
NET_U12_1: R23.1, R24.1, U12.1
NET_U12_3: R25.2, R26.1, U12.3
NET_U12_4: R22.1, U12.4, U15.2
NET_U13_1: R2.1, U13.1, U13.2
PROC_CAN_RX: U1.32, U3.4
PROC_CAN_TX: U1.33, U3.1
PROC_SPI1_MISO: U1.16, U6.16
PROC_SPI1_MOSI: U1.17, U6.2
PROC_SPI1_NSS: R13.1, U1.14, U6.3
PROC_SPI1_SCK: U1.15, U6.4
PROC_SPI2_MISO: U1.27, U2.2
PROC_SPI2_MOSI: U1.28, U2.5
PROC_SPI2_NSS: R10.1, U1.25, U2.1
PROC_SPI2_SCK: U1.21, U2.6
VCC_S1_7V4: C18.1, C20.1, C23.1, C24.1, J1.1, R15.2, R19.2, U10.4, U11.8
VCC_TIER1_1V8: C1.1, C2.1, C3.1, C4.1, C5.1, C6.1, C10.1, C12.1, C13.1, C14.1, C15.1, C16.1, C19.1, C22.1, C25.1, F1.2, R1.2, R3.2, R4.2, R5.2, R9.2, R10.2, R11.2, R13.2, R14.2, R16.1, R22.2, R23.2, R25.1, U1.1, U1.24, U1.48, U2.8, U5.8, U6.5, U8.4, U9.4, U10.5, U12.6, U15.5
VCC_TIER1_3V3: C7.1, C11.1, C21.1, R6.2, R18.2, R20.1, U1.36, U3.3, U11.1

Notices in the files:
parts and their libraries:
circuit_tree: (C) 2014 Tomasz Boleslaw CEDRO, cederom@tlen.pl, http://www.tomek.cedro.info.
